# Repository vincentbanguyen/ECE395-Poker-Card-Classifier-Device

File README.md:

https://github.com/user-attachments/assets/9b204c32-8d50-4713-b9ab-50e7000abaa3

## Introduction ##
Our project is a poker card classifier.  The device works by first placing a card on the white slot. A picture of the card is taken when the button is pressed, and the image is processed into RGB values and fed into a neural network. The neural network outputs the probabilities of each card, and displays the most probable card on the LCD display. 

## Specifications ## 
STM32H743VIT6 Chip
OV7670 Camera
USB-C Receptacle (USB4085)
5V to 3.3V LDO (TC1262-33)
1602 LCD Display

## Block Diagram ##

## Design Process ##
### Step 1: Schematic and PCB Design ###
We started the project by designing our PCB which connected the STM32 microcontroller with all other components. We chose a 2-layer design for our PCB, with the front layer being grounded and the back layer being 3V3. As different chips are driven by different voltages, the board receives 5V power input from the USB-C receptacle, and 3.3V voltage is obtained from the 5V to 3.3V LDO. We decoupled both 5V and 3V3 input with decoupling capacitors, so that our design became less noise-sensitive. 

In order to effectively utilize the space on the PCB, we decided to split 24 camera pins into 4 different headers centered around the microcontroller, such that there wouldn’t be a long header occupying the entire board. The headers for the LCD display and the serial port are placed around the STM32 chip similar to the camera pins. The left part of our PCB contains three buttons, which control the BOOT pin, the reset pin, and the capture pin. All the buttons have a pull-down resistor such that the pins will be grounded when the buttons are not pressed. 

### Step 2: Test UART on Nucleo-Board ###
Configuring UART properly is very crucial to this project, as we not only need the information for debugging, but also log data from the console to generate our image. Since the OV7670 camera needs  I2C and DMCI pins, we configured UART4 to be our UART communication port with a baud rate of 115200. The TX and RX pins on the chip are connected to the RX and TX pins on the serial port to transfer data in the right direction.

Since the console doesn’t have access to printf directly, we realize printing through the sprintf function to send whatever string we need to print. Below is an example on how this sprintf method works:

Buffer is a string with the size of 100 characters, and sprintf function will define the content of the buffer variable with the desired test string we try to print. Afterwards, the HAL_UART_Transmit function will output the buffer from the uart4 port. By doing so, we accomplish printing strings that contain both characters and numbers, realizing the functionality of printf.

### Step 3: Test I2C for LCD on a Nucleo-Board ###
LCD 1602 is the first device that needs to communicate through the I2C protocol, hence we allocate I2C2 for the LCD display. We implemented the lcd_send_cmd function to configure the lcd and the lcd_send_data function to send strings into the display. Both functions rely on the HAL_I2C_Master_Transmit function to accomplish the data transfer.

When a new string is sent to the LCD, the new string will be appended to the current content of the LCD. Therefore, we implement the lcd_clear function to clear out the screen such that only the new string would be displayed:

###Step 4: Use I2C to write to Camera Registers ###
Similar to LCD 1602, the OV7670 - STM32 communication is realized through the I2C protocol. We implement the ov7670_write and ov7670_read functions to transfer data into / from the registers in the camera module. 

### Step 5: Read Camera Data Output ###

The OV7670 has a DCMI (Digital-Camera-Interface) where it outputs 8 data signals into the chip’s DCMI. The data is temporarily stored in a 32-bit register, and a DMA request is generated. The DMA (Direct-Memory-Access) controller then transfers the data into our requested memory address, which is our imagedata buffer. 

We used UART to print and read our imagedata buffer index by index into the console. 
Our camera outputs in RGB565 format. This means the first 5 bits are red, next 6 bits are green, and the last 5 bits are blue. Each index is a 32-bit word, so each index is 2 pixels and each pixel is 2 bytes large.

### Step 6: Convert Card Log into a JPG image ###
In order to see the camera output image, we have to convert the RGB log into a JPG image. We did this by creating a python script called “log2img.py” and the pillow library to interpret each line in the log as 2 pixels with RGB values, and arranging them into a 128 by 128 array. The Pillow library then can convert this array into a JPG image that we can view.

### Step 7: Assess Image and Adjust Camera registers for Desired Image Quality ###

After getting a viewable image from the log, we adjusted the registers to produce an image RGB565 format and in QCIF (176 x 144) resolution. At first, the color in our images seemed to be incorrect, and we referenced another camera project that adjusted the color matrix registers in the camera. Writing their same values seemed to correctly calibrate our outputs, and now we are able to distinguish black and red cards.

### Step 8: Collect Logs of All Cards and Create Dataset ###
When using the device, the captured photos will have slight variations due to the environment. Since we only collected a single image for each card, it’s important to create synthetic images with slight variations by slightly transforming each card image with some rotation, and brightness, and contrast. Pytorch has helpful transform functions to do so. 

### Step 9: Design Convolutional Neural Network ###

The image above is a popular architecture for image classification, so our project implemented a similar but simpler design since it was important to keep our model as small as possible in order to fit onto the chip. We aimed to keep it below 1 MB. 

Our architecture above accepts a 128x128 image tensor, and passes through two convolution layers, and 2 fully connected layers, and outputs 54 probabilities.

### Step 10: Train and Assess CNN ###
The basic idea of training our model was to iterate through the training dataset and input it into the neural network, and compare its prediction to the actual value, and adjust the weights to minimize loss. Doing this enough times will result in optimized weights that will more accurately predict our cards. We can then assess our model by iterating through our test dataset images and input them into the model, and see the predicted vs. actual image.

### Step 11: Convert Pytorch Model into TFLite Model ###
The STM32CubeIDE allows us to upload a TFLite Model. Since we developed our model using pytorch, we had to convert it into a Tensorflow model, then into a TensorFlow Lite model.

### Step 12: Using a TFLite Model with STM32 ###
We first uploaded the TFLITE model into STM32CubeIDE through the .ioc file. The specific steps to do this are documented on ST’s CubeAI website. After the model is uploaded, the configuration file auto generates an “app_x-cube-ai.c file” where we can interface with the model.

There are three steps within this file in order to get a prediction:

Acquire and Process:
The first step is to populate the neural network’s input buffer with normalized RGB values. Note that our order into the buffer was pixel 2 GBR and then pixel 1 GBR. 

Run Network with Input
After populating the input buffer, we call ai_run(), which will run the model’s inference code and populate the output data with the 54 probabilities. 

Post Process
We iterated through the output buffer that contained probabilities, and the largest probability is our prediction. We then print out this prediction into the LCD display.

### Challenges  ###
The first challenge we had was when trying to perform I2C to display a string on the LCD display. The issue was that the pin headers on the nucleo-board covered the pin name, so we connected the wrong pin for SDA. 

After getting I2C to work for the LCD, we attempted to use I2C to write to the camera register. The HAL_UART_MASTER_TRANSMIT and HAL_UART_MASTER_RECEIVE kept returning an error code, but we realized that the Camera Reset should be active low instead of active high.

After correctly configuring the camera through writing to its registers, we attempted to read camera data using DCMI. The HAL_DCMI_START_DMA function is supposed to use the DMA to copy over DCMI data from the camera into our specified image_buffer, but the image_buffer didn’t seem to get populated. Online sources suggested to disable D-Cache, and we found out that VSYNC wasn’t properly soldered to the nucleo-board. The combination of these fixed our issue, and we were able to receive image data into our image buffer.

When we attempted to program the PCB, we received “No ST-Link Device Found”. We first assumed that the clone programmer was broken, and that a genuine one was needed. However, we used the multimeter to determine that the VDD pins were receiving 2.8 V instead of the required 3.3V. We realized that our decoupling schematic was incorrect, so we manually correct it onto the board. Another issue was that we forgot to power VREF, so we connected it to VDD. These two fixes allowed us to program the board.

Another challenge we had was collecting our training data for the neural network. Our approach was to manually get all of the cards log data through printing through the serial port, and converting the log data into images on a python script. A better way would have been encoding the image data and saving them all to an SD card.

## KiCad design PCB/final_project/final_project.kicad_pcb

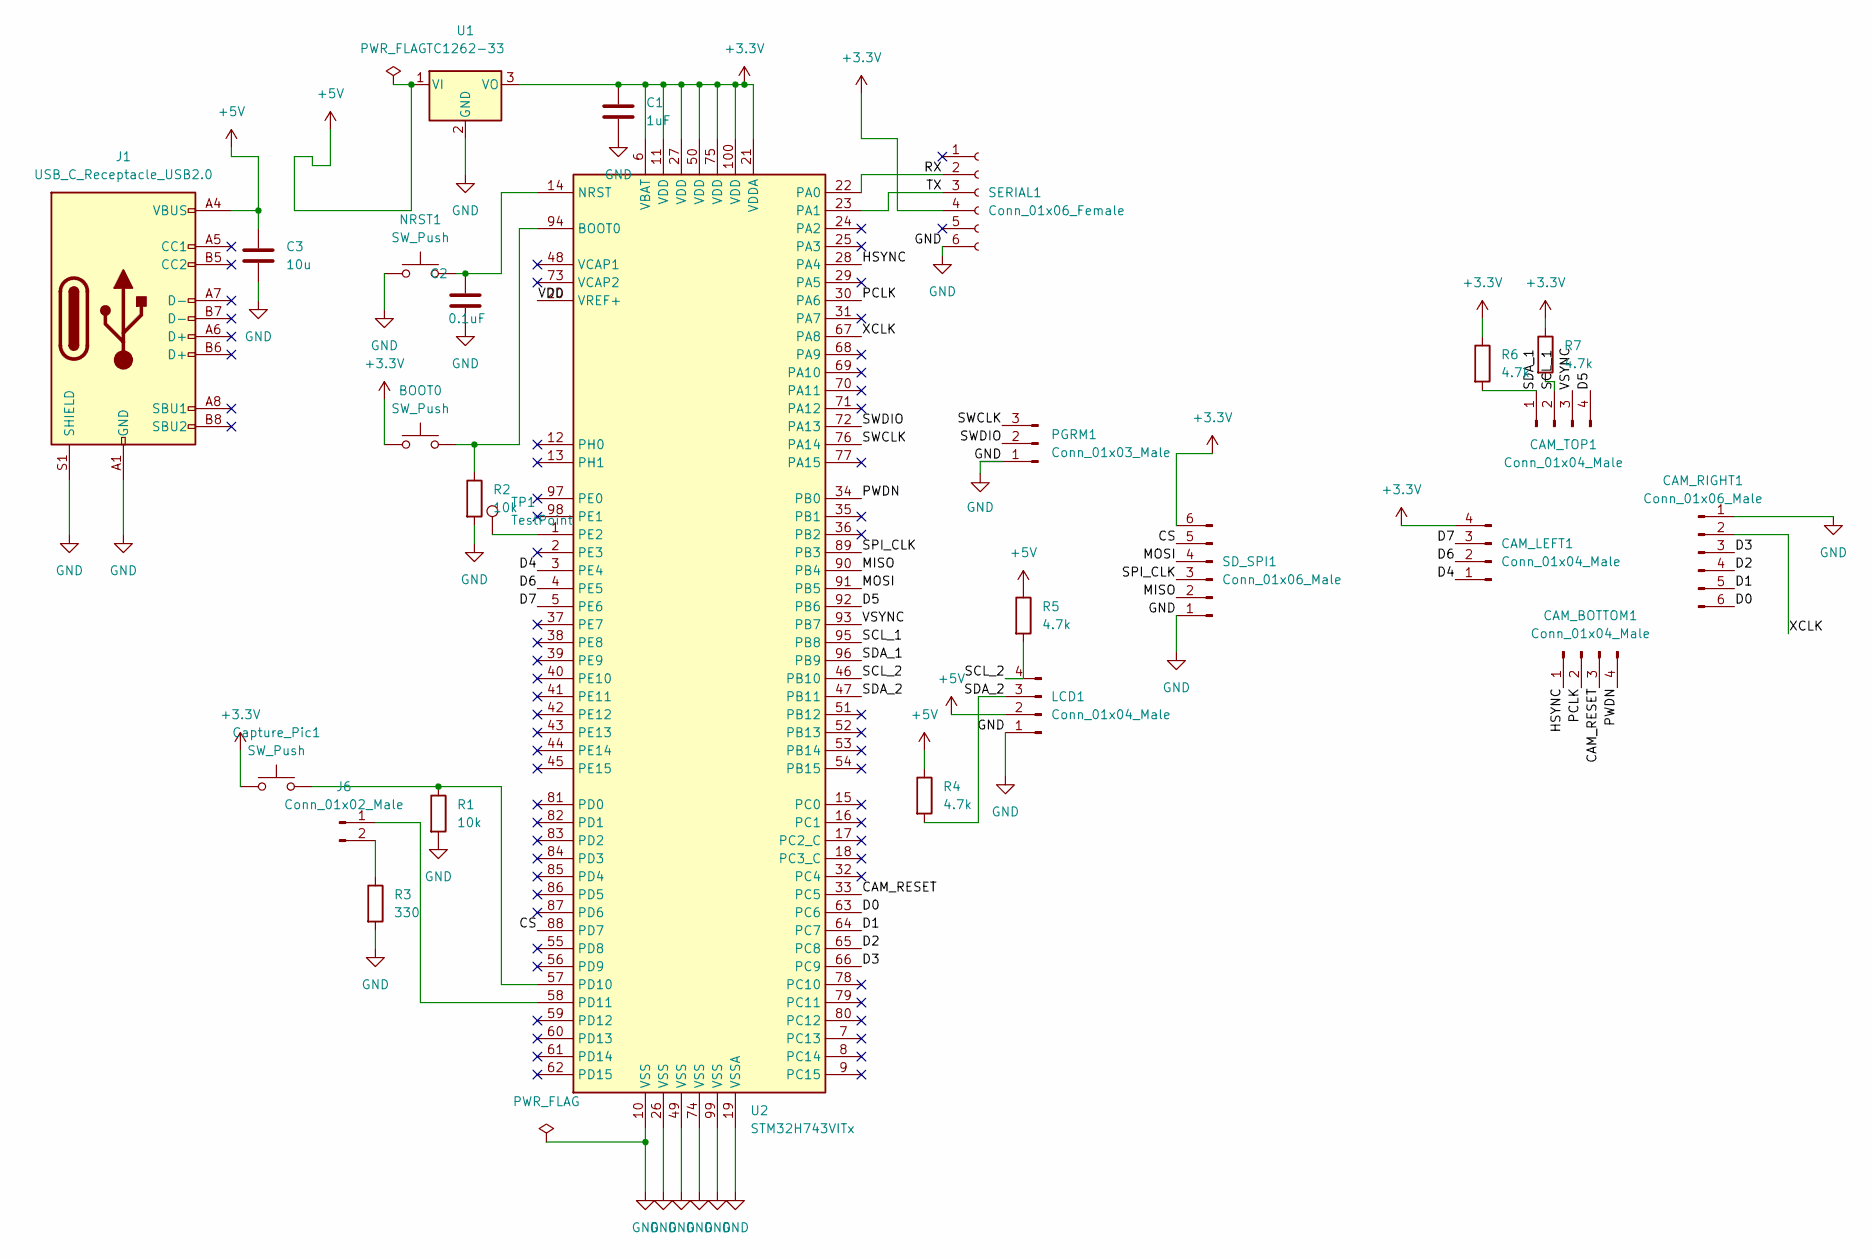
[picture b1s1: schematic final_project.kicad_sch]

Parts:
BOOT0: SW_Push; SW_PUSH_6mm_H4.3mm
C1: 1uF; C_0805_2012Metric_Pad1.18x1.45mm_HandSolder
C2: 0.1uF; C_0805_2012Metric_Pad1.18x1.45mm_HandSolder
C3: 10u; C_0805_2012Metric_Pad1.18x1.45mm_HandSolder
CAM_BOTTOM1: Conn_01x04_Male; PinHeader_1x04_P2.54mm_Vertical
CAM_LEFT1: Conn_01x04_Male; PinHeader_1x04_P2.54mm_Vertical
CAM_RIGHT1: Conn_01x06_Male; PinHeader_1x06_P2.54mm_Vertical
CAM_TOP1: Conn_01x04_Male; PinHeader_1x04_P2.54mm_Vertical
Capture_Pic1: SW_Push; SW_PUSH_6mm_H4.3mm
J1: USB_C_Receptacle_USB2.0; USB_C_Receptacle_GCT_USB4085
J6: Conn_01x02_Male; PinHeader_1x02_P2.54mm_Vertical
LCD1: Conn_01x04_Male; PinHeader_1x04_P2.54mm_Vertical
NRST1: SW_Push; SW_PUSH_6mm_H4.3mm
PGRM1: Conn_01x03_Male; PinHeader_1x03_P2.54mm_Vertical
R1, R2: 10k; R_0805_2012Metric_Pad1.20x1.40mm_HandSolder
R3: 330; R_0805_2012Metric_Pad1.20x1.40mm_HandSolder
R4, R5, R6, R7: 4.7k; R_0805_2012Metric_Pad1.20x1.40mm_HandSolder
SD_SPI1: Conn_01x06_Male; PinHeader_1x06_P2.54mm_Vertical
SERIAL1: Conn_01x06_Female; PinSocket_1x06_P2.54mm_Vertical
TP1: TestPoint; TestPoint_Keystone_5010-5014_Multipurpose
U1: TC1262-33; SOT-223-3_TabPin2
U2: STM32H743VITx; LQFP-100_14x14mm_P0.5mm

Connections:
+3V3: BOOT0.1, C1.1, CAM_LEFT1.4, Capture_Pic1.1, R6.1, R7.1, SD_SPI1.6, SERIAL1.4, U1.3 (VO), U2.6 (VBAT), U2.11 (VDD), U2.21 (VDDA), U2.27 (VDD), U2.50 (VDD), U2.75 (VDD), U2.100 (VDD)
+5V: C3.1, J1.A4 (VBUS), J1.A9 (VBUS), J1.B4 (VBUS), J1.B9 (VBUS), LCD1.2, R4.1, R5.1, U1.1 (VI)
/CAM_RESET: CAM_BOTTOM1.3, U2.33 (PC5)
/CS: SD_SPI1.5, U2.88 (PD7)
/D0: CAM_RIGHT1.6, U2.63 (PC6)
/D1: CAM_RIGHT1.5, U2.64 (PC7)
/D2: CAM_RIGHT1.4, U2.65 (PC8)
/D3: CAM_RIGHT1.3, U2.66 (PC9)
/D4: CAM_LEFT1.1, U2.3 (PE4)
/D5: CAM_TOP1.4, U2.92 (PB6)
/D6: CAM_LEFT1.2, U2.4 (PE5)
/D7: CAM_LEFT1.3, U2.5 (PE6)
/HSYNC: CAM_BOTTOM1.1, U2.28 (PA4)
/MISO: SD_SPI1.2, U2.90 (PB4)
/MOSI: SD_SPI1.4, U2.91 (PB5)
/PCLK: CAM_BOTTOM1.2, U2.30 (PA6)
/PWDN: CAM_BOTTOM1.4, U2.34 (PB0)
/RX: SERIAL1.2, U2.22 (PA0)
/SCL_1: CAM_TOP1.2, R7.2, U2.95 (PB8)
/SCL_2: LCD1.4, R5.2, U2.46 (PB10)
/SDA_1: CAM_TOP1.1, R6.2, U2.96 (PB9)
/SDA_2: LCD1.3, R4.2, U2.47 (PB11)
/SPI_CLK: SD_SPI1.3, U2.89 (PB3)
/SWCLK: PGRM1.3, U2.76 (PA14)
/SWDIO: PGRM1.2, U2.72 (PA13)
/TX: SERIAL1.3, U2.23 (PA1)
/VDD: U2.20 (VREF+)
/VSYNC: CAM_TOP1.3, U2.93 (PB7)
/XCLK: CAM_RIGHT1.2, U2.67 (PA8)
GND: C1.2, C2.2, C3.2, CAM_RIGHT1.1, J1.A1 (GND), J1.A12 (GND), J1.B1 (GND), J1.B12 (GND), J1.S1 (SHIELD), LCD1.1, NRST1.1, PGRM1.1, R1.2, R2.2, R3.2, SD_SPI1.1, SERIAL1.6, U1.2 (GND), U2.10 (VSS), U2.19 (VSSA), U2.26 (VSS), U2.49 (VSS), U2.74 (VSS), U2.99 (VSS)
unnamed: BOOT0.2, R2.1, U2.94 (BOOT0)
unnamed: C2.1, NRST1.2, U2.14 (NRST)
unnamed: Capture_Pic1.2, R1.1, U2.57 (PD10)
unnamed: J6.1, U2.58 (PD11)
unnamed: J6.2, R3.1
unnamed: TP1.1, U2.1 (PE2)

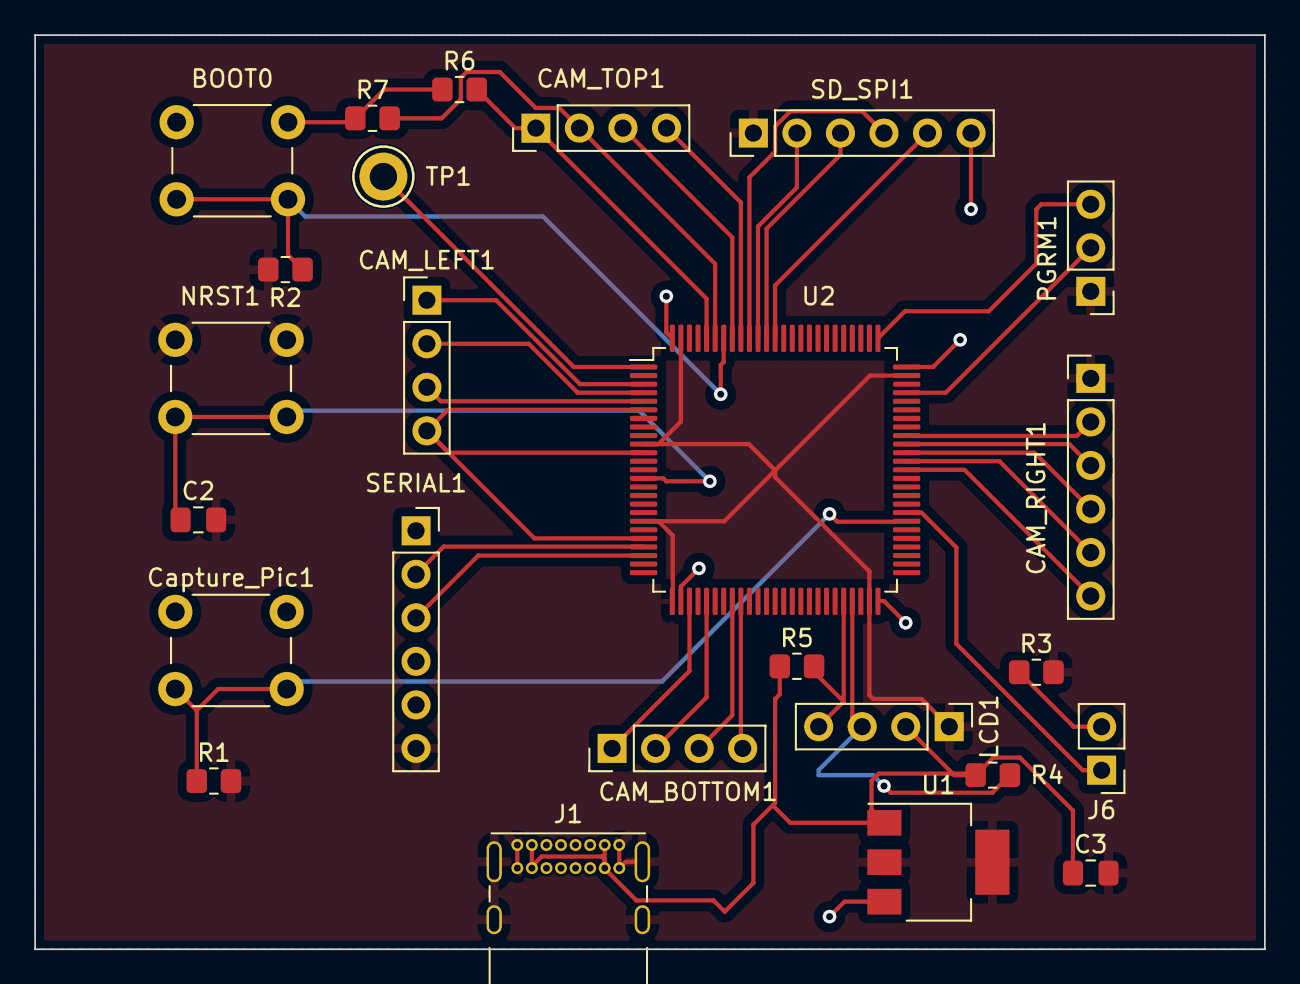
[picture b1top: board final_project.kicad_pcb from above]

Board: 2 copper layers, 71.8 x 53.3 mm, 25 parts (0 on the bottom side), 35 nets.

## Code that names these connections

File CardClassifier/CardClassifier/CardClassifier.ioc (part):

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Mcu.Name=STM32H743VITx
Mcu.Package=LQFP100
Mcu.UserName=STM32H743VITx
PA0.Mode=Asynchronous
PA0.Signal=UART4_TX
PA1.Mode=Asynchronous
PA1.Signal=UART4_RX
PA4.GPIOParameters=GPIO_Speed,GPIO_PuPd
PA4.GPIO_PuPd=GPIO_PULLDOWN
PA4.GPIO_Speed=GPIO_SPEED_FREQ_VERY_HIGH
PA4.Mode=Slave_8_bits_External_Synchro
PA4.Signal=DCMI_HSYNC
PA6.GPIOParameters=GPIO_Speed,GPIO_PuPd
PA6.GPIO_PuPd=GPIO_PULLDOWN
PA6.GPIO_Speed=GPIO_SPEED_FREQ_VERY_HIGH
PA6.Mode=Slave_8_bits_External_Synchro
PA6.Signal=DCMI_PIXCLK
PA8.Mode=Clock-out-1
PA8.Signal=RCC_MCO_1
PB0.GPIOParameters=PinState,GPIO_Label
PB0.GPIO_Label=PWDN
PB0.PinState=GPIO_PIN_SET
PB0.Signal=GPIO_Output
PB10.GPIOParameters=GPIO_Pu
PB10.GPIO_Pu=GPIO_NOPULL
PB10.Mode=I2C
PB10.Signal=I2C2_SCL
PB11.GPIOParameters=GPIO_Pu
PB11.GPIO_Pu=GPIO_NOPULL
PB11.Mode=I2C
PB11.Signal=I2C2_SDA
PB7.GPIOParameters=GPIO_Speed,GPIO_PuPd
PB7.GPIO_PuPd=GPIO_PULLDOWN
PB7.GPIO_Speed=GPIO_SPEED_FREQ_VERY_HIGH
PB7.Mode=Slave_8_bits_External_Synchro
PB7.Signal=DCMI_VSYNC
PB8.GPIOParameters=GPIO_Pu
PB8.GPIO_Pu=GPIO_PULLUP
PB8.Mode=I2C
PB8.Signal=I2C1_SCL
PB9.GPIOParameters=GPIO_Pu
PB9.GPIO_Pu=GPIO_PULLUP
PB9.Mode=I2C
PB9.Signal=I2C1_SDA
PC5.GPIOParameters=GPIO_Label
PC5.GPIO_Label=CAM_RST
PC5.Signal=GPIO_Output
PC6.GPIOParameters=GPIO_Speed,GPIO_PuPd
PC6.GPIO_PuPd=GPIO_PULLDOWN
PC6.GPIO_Speed=GPIO_SPEED_FREQ_VERY_HIGH
PC6.Mode=Slave_8_bits_External_Synchro
PC6.Signal=DCMI_D0
PC7.GPIOParameters=GPIO_Speed,GPIO_PuPd
PC7.GPIO_PuPd=GPIO_PULLDOWN
PC7.GPIO_Speed=GPIO_SPEED_FREQ_VERY_HIGH
PC7.Mode=Slave_8_bits_External_Synchro
PC7.Signal=DCMI_D1
PC8.GPIOParameters=GPIO_Speed,GPIO_PuPd
PC8.GPIO_PuPd=GPIO_PULLDOWN
PC8.GPIO_Speed=GPIO_SPEED_FREQ_VERY_HIGH
PC8.Mode=Slave_8_bits_External_Synchro
PC8.Signal=DCMI_D2
PC9.GPIOParameters=GPIO_Speed,GPIO_PuPd
PC9.GPIO_PuPd=GPIO_PULLDOWN
PC9.GPIO_Speed=GPIO_SPEED_FREQ_VERY_HIGH
PC9.Mode=Slave_8_bits_External_Synchro
PC9.Signal=DCMI_D3
PD10.GPIOParameters=GPIO_Label
PD10.GPIO_Label=CAPTURE
PD10.Signal=GPIO_Output
PD11.GPIOParameters=GPIO_Label
PD11.GPIO_Label=LED
PD11.Signal=GPIO_Output
PD3.GPIOParameters=GPIO_Speed,GPIO_PuPd
PD3.GPIO_PuPd=GPIO_PULLDOWN
PD3.GPIO_Speed=GPIO_SPEED_FREQ_VERY_HIGH
PD3.Mode=Slave_8_bits_External_Synchro
PD3.Signal=DCMI_D5
PE2.Signal=GPIO_Output
PE4.GPIOParameters=GPIO_Speed,GPIO_PuPd
PE4.GPIO_PuPd=GPIO_PULLDOWN
PE4.GPIO_Speed=GPIO_SPEED_FREQ_VERY_HIGH
PE4.Mode=Slave_8_bits_External_Synchro
PE4.Signal=DCMI_D4
PE5.GPIOParameters=GPIO_Speed,GPIO_PuPd
PE5.GPIO_PuPd=GPIO_PULLDOWN
PE5.GPIO_Speed=GPIO_SPEED_FREQ_VERY_HIGH
PE5.Mode=Slave_8_bits_External_Synchro
PE5.Signal=DCMI_D6
PE6.GPIOParameters=GPIO_Speed,GPIO_PuPd
PE6.GPIO_PuPd=GPIO_PULLDOWN
PE6.GPIO_Speed=GPIO_SPEED_FREQ_VERY_HIGH
PE6.Mode=Slave_8_bits_External_Synchro
PE6.Signal=DCMI_D7
PH0-OSC_IN\ (PH0).Mode=HSE-External-Clock-Source
PH0-OSC_IN\ (PH0).Signal=RCC_OSC_IN
RCC.HSE_VALUE=8000000
RCC.SYSCLKFreq_VALUE=480000000
RCC.SYSCLKSource=RCC_SYSCLKSOURCE_PLLCLK
RCC.SYSCLKSourceVirtual=RCC_SYSCLKSOURCE_PLLCLK
board=custom

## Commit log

2024-04-02 add initial files
2024-04-06 Add working ml model
2024-04-06 modify rgb log2img
2024-04-06 correctly extract rgb
2024-04-06 fixed rgb
2024-04-06 Optimized for ov7670
2024-04-07 generated large tflite model
2024-04-08 creataed custom cnn, tflite model is 400 kb
2024-04-09 Add LCD Support
2024-04-10 Add CAM I2C
2024-04-10 Add CAM Image Capture + Log
2024-04-10 Add AI boilerplate
2024-04-14 add new 128 x 128 ml model
2024-04-16 Update Hardware
2024-04-16 add DQ log
2024-04-16 add DQ log v2
2024-04-16 add more logs
2024-04-16 added 1/3 logs
2024-04-19 added 1/2 logs
2024-04-19 added PCB and more logs
2024-04-19 Complete log
2024-04-19 128 x 128 RGB model
2024-04-23 reduce variation in synthesized dataset
2024-04-23 New log
2024-04-26 White LED Logs
2024-04-26 CT log fixed
2024-04-26 Finalize STM32 Code
2024-04-26 new model with white_led_log
